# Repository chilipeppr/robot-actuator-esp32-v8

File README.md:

# robot-actuator-esp32-v8
This is the repo for the robot actuator v8 based on an ESP32 as the brains of each robot arm actuator.

This repository contains the latest design for the small actuator including:
- PCB schematic and board file (Eagle)
- Bill of Materials
- Fusion 360 files
- STL files for 3D printing
- NodeMCU ESP32 for Lua firmware with touch module, pulse counter module, RMT TX module, and gpiomatrix module.
- Lua code for actuator
- Link to ChiliPeppr http://chilipeppr.com/arm workspace to control the actuator and to ChiliPeppr ESP32 for Lua workspace for uploading code to the ESP32 device http://chilipeppr.com/esp32
- Heat management test results
- Youtube videos

This actuator is based on the amazing design of Jeff Kerr's (LoboCNC on Thingiverse) 3D printed robot arm WE-R2.4 six axis robot arm. https://www.thingiverse.com/thing:3327968

# Eagle Files

The main PCB board in Eagle.

Top

Bottom

The touch PCB board in Eagle.

# Ordering PCBs

When ordering PCBs, keep in mind the thickness of the main PCB is 1.0 mm while the touch PCB is 1.2 mm. A white soldermask is recommended, but not important.

Main PCB is 1.0 mm thickness

Touch PCB is 1.2 mm thickness

# Fusion 360

The CAD files in Fusion360.

# ChiliPeppr

ChiliPeppr Robot Arm Workspace (Work in progress)
http://chilipeppr.com/arm

ChiliPeppr ESP32 for Lua Workspace for editing/uploading code
http://chilipeppr.com/esp32

# Heat Test

# Youtube Videos

Part 1
https://www.youtube.com/watch?v=tEbJV32GyYU

Part 2
https://www.youtube.com/watch?v=RdmdFIhCo4M

Part 3
https://youtu.be/4o3d7_WZ_DQ

<!-- # Pins Used on ESP32

|GPIO|Used|Input|Output|Notes|
|----|-----|------|-----|
|0|Yes|Yes|Yes|motor.pinDir|
|1|TX pin|OK|debug output at boot|
|2|OK|OK|connected to on-board LED|
|3|OK|RX pin|HIGH at boot|
|4|OK|OK|
|5|OK|OK|outputs PWM signal at boot|
|6|x|x|connected to the integrated SPI flash|
|7|x|x|connected to the integrated SPI flash|
|8|x|x|connected to the integrated SPI flash|
|9|x|x|connected to the integrated SPI flash|
|10|x|x|connected to the integrated SPI flash|
|11|x|x|connected to the integrated SPI flash|
|12|OK|OK|boot fail if pulled high|
|13|OK|OK|
|14|OK|OK|outputs PWM signal at boot|
|15|OK|OK|outputs PWM signal at boot|
|16|OK|OK|
|17|OK|OK|
|18|OK|OK|
|19|OK|OK|
|21|OK|OK|
|22|OK|OK|
|23|OK|OK|
|25|OK|OK|
|26|OK|OK|
|27|OK|OK|
|32|OK|OK|
|33|OK|OK|
|34|OK|input only|
|35|OK|input only|
|36|OK|input only|
|39|OK|input only| -->

# Bill of Materials

| Ref    | Part                                                   |  Price   |  Quantity  |  Ext Price  | URL                                                                                                                                                 | Notes                                                                                                                                                                                                                                                                                                                                                  |
|--------|--------------------------------------------------------|----------|------------|-------------|-----------------------------------------------------------------------------------------------------------------------------------------------------|--------------------------------------------------------------------------------------------------------------------------------------------------------------------------------------------------------------------------------------------------------------------------------------------------------------------------------------------------------|
|        |                                                        |          |            |             |                                                                                                                                                     |                                                                                                                                                                                                                                                                                                                                                        |
|        | PCB                                                    |          |            |  $-         |                                                                                                                                                     |                                                                                                                                                                                                                                                                                                                                                        |
|        | ESP32 Wemos Mini                                       |  $4.05   |  1         |  $4.05      | https://www.aliexpress.com/item/32839344778.html                                                                                                    |                                                                                                                                                                                                                                                                                                                                                        |
|        | 2x10 Pin Header Female for ESP32                       |  $0.12   |  2         |  $0.24      | https://lcsc.com/product-detail/Pin-Header-Female-Header_Boom-Precision-Elec-2-54mm-2-10-Straight-Female-header_C30867.html                         | Solder to the ESP32 board                                                                                                                                                                                                                                                                                                                              |
| C1     | 2x10 Pin Header Male for ESP32                         |  $0.10   |  1         |  $0.10      | https://lcsc.com/product-detail/Pin-Header-Female-Header_Shenzhen-Cankemeng-Headers-Pins-2-10P-2-54mm-Straight-line_C124359.html                    | Solder to main PCB                                                                                                                                                                                                                                                                                                                                     |
|        | DRV8825                                                |  $0.88   |  1         |  $0.88      | https://www.aliexpress.com/item/33010878323.html                                                                                                    | The most popular stepper driver out there. Simple and easy.                                                                                                                                                                                                                                                                                            |
|        | 100uF 50V Capacitor for DRV8825                        |  $0.13   |  1         |  $0.13      | https://lcsc.com/product-detail/Aluminum-Electrolytic-Capacitors-Leaded_PANASONIC-EEUFM1H101_C128473.html                                           | The big capacitor for stepper motor driver                                                                                                                                                                                                                                                                                                             |
|        | DC to DC 24V to 5V Converter                           |  $0.48   |  1         |  $0.48      | https://www.aliexpress.com/item/32796268715.html                                                                                                    | Little board from Aliexpress to get us to 5V on the cheap                                                                                                                                                                                                                                                                                              |
|        | Fan 25mm 12V                                           |  $1.08   |  1         |  $1.08      | https://www.aliexpress.com/item/33026177502.html                                                                                                    | Silent fan that we overdrive to 20v for brief periods if heat spikes, otherwise we leave it off                                                                                                                                                                                                                                                        |
| R3     | Fan Mosfet FDV301N 25V 220mA SOT-23                    |  $0.04   |  1         |  $0.04      | https://lcsc.com/product-detail/MOSFET_ON-Semicon_FDV301N_ON-Semicon-ON-FDV301N_C15310.html                                                         | Allows PWM speed control of fan. Run around 20Hz.                                                                                                                                                                                                                                                                                                      |
| R4     | Fan Diode Protector 100V 300mA SOD-123                 |  $0.02   |  1         |  $0.02      | https://lcsc.com/product-detail/Switching-Diode_DIODES_1N4148W-7-F_1N4148W-7-F_C83528.html                                                          | When fan switches off from Mosfet, it generates back current, so this diode lets it loop back into the fan to get absorbed                                                                                                                                                                                                                             |
|        | Fan 100Ohm gate resistor 0402                          |  $0.01   |  1         |  $0.01      | https://lcsc.com/product-detail/Chip-Resistor-Surface-Mount_100R-100R-1_C106232.html                                                                | Absorbs feedback attenuation                                                                                                                                                                                                                                                                                                                           |
|        | Fan 1MOhm pull-down resistor 0402                      |  $0.01   |  1         |  $0.01      | https://lcsc.com/product-detail/Chip-Resistor-Surface-Mount_1MR-105-5_C144054.html                                                                  | Pulldown resistor to ground to shut off mosfet                                                                                                                                                                                                                                                                                                         |
|        | JST XH Male Connector for fan                          |  $0.04   |  1         |  $0.04      | https://lcsc.com/product-detail/Wire-To-Board-Wire-To-Wire-Connector_JST-Sales-America_B2B-XH-A-LF-SN_JST-Sales-America-B2B-XH-A-LF-SN_C158012.html |                                                                                                                                                                                                                                                                                                                                                        |
|        | JST XH Crimp Connector for fan wire                    |  $0.01   |  2         |  $0.02      | https://lcsc.com/product-detail/New-Arrivals_JST-Sales-America-SXH-001T-P0-6N_C385122.html                                                          | In case you have to reterminate the fan wire, get these crimp connectors. You need a crimp tool.                                                                                                                                                                                                                                                       |
|        | JST XH Female Connector for fan wire                   |  $0.02   |  1         |  $0.02      | https://lcsc.com/product-detail/Rectangular-Connectors-Housings_JST-Sales-America_XHP-2_JST-Sales-America-XHP-2_C144401.html                        | In case you have to reterminate the fan wire, get this female housing to slide the crimp connectors into                                                                                                                                                                                                                                               |
|        | WS2812B White                                          |  $0.15   |  1         |  $0.15      | https://www.aliexpress.com/item/32960205936.html                                                                                                    | Break off one LED and solder to side of PCB at 90 degree angle. Connect center pin to DIN, not DOUT.                                                                                                                                                                                                                                                   |
|        | Red LED 0805                                           |  $0.02   |  3         |  $0.06      | https://lcsc.com/product-detail/Light-Emitting-Diodes-LED_0805-Red-LED-Iv-61mcd-Typ-atIF-20mA_C72037.html                                           | Indicator LEDs                                                                                                                                                                                                                                                                                                                                         |
| R5, R2 | 1KOhm current limit resistor for LED 0402              |  $0.01   |  2         |  $0.02      | https://lcsc.com/product-detail/Chip-Resistor-Surface-Mount_1KR-1001-1_C106235.html                                                                 | The LEDs on the 3.3v bus for step and fan indicator use 1K to give LED about 1ma of current so it lights up very dim, but enough to indicate status.                                                                                                                                                                                                   |
| R6     | 2KOhm current limit resistor for power LED 0402        |  $0.01   |  1         |  $0.01      | https://lcsc.com/product-detail/Chip-Resistor-Surface-Mount_Uniroyal-Elec-0402WGF2001TCE_C4109.html                                                 | The power LED is on a 5v bus. 2K gives it about 1.5ma of current for a dim indicator.                                                                                                                                                                                                                                                                  |
|        | 8 Pin Female Header 2.54mm                             |  $0.14   |  2         |  $0.28      | https://lcsc.com/product-detail/Pin-Header-Female-Header_Changjiang-Connectors-A2541HWV-8P_C225505.html                                             | 2 needed for DRV8825 connection to main PCB.                                                                                                                                                                                                                                                                                                           |
|        | 4 Pin Female Header 2.54mm                             |  $0.07   |  3         |  $0.22      | https://lcsc.com/product-detail/Pin-Header-Female-Header_Shenzhen-Cankemeng-Female-header-1-4P-2-54mm-Straight-line_C124413.html                    | 1 for DC to DC, 2 for touch sensor PCB connection                                                                                                                                                                                                                                                                                                      |
|        | 3 Pin Female Header 2.54mm                             |  $0.06   |  2         |  $0.11      | https://lcsc.com/product-detail/Pin-Header-Female-Header_Shenzhen-Cankemeng-22025403P00CKMT_C146690.html                                            | One for Hall sensor, one for TMP36.                                                                                                                                                                                                                                                                                                                    |
|        | 2 Pin Female Header 2.54mm                             |  $0.03   |  4         |  $0.10      | https://lcsc.com/product-detail/Pin-Header-Female-Header_Boom-Precision-Elec-2-54-1-2PFemale_C49661.html                                            | 2 for incoming 20v from slip ring. 2 for outgoing 20v to slip ring.                                                                                                                                                                                                                                                                                    |
|        | JST PH B4B-K-S Male Header for Stepper                 |  $0.17   |  1         |  $0.17      | https://lcsc.com/product-detail/Wire-To-Board-Wire-To-Wire-Connector_JST-Sales-America_B4B-PH-K-LF-SN_JST-Sales-America-B4B-PH-K-LF-SN_C265289.html | Socket soldered to PCB                                                                                                                                                                                                                                                                                                                                 |
|        | JST PHR-4 Female Header for Stepper Cable              |  $0.02   |  1         |  $0.02      | https://lcsc.com/product-detail/Connectors_JST_PHR-4_PHR-4-4P-pitch2-0mm-Plastic-shell_C111514.html                                                 | End of wire crimped connector                                                                                                                                                                                                                                                                                                                          |
| C2     | JST SPH Crimp Connector                                |  $0.01   |  4         |  $0.03      | https://lcsc.com/product-detail/Rectangular-Connectors-Contacts_JST_SPH-002T-P0-5S_SPH-002T-P0-5S-PH-T-PH-2-0_C111515.html                          | Individual crimp connectors. You'll need a crimping tool.                                                                                                                                                                                                                                                                                              |
|        | Toggle Switch                                          |  $0.12   |  1         |  $0.12      | https://lcsc.com/product-detail/Toggle-Switches_Korean-Hroparts-Elec-K3-1260D-L1_C92657.html                                                        | Toggle on/off the 20v to all components                                                                                                                                                                                                                                                                                                                |
|        | Pin Male Header Right Angle 2.54mm (40 pins breakaway) |  $0.44   |  2         |  $0.88      | https://www.digikey.com/product-detail/en/0022286043/WM22771-ND/3158673                                                                             | Right angle needed for touch sensor connection. Actually, I had to create my own right angle ones from straight ones to be long enough. They need to be about 10mm long from the touch PCB down to the pin headers, so buy the longest straight ones you can and bend them, then cut to size after you try to fit. Or, you can buy them from digikey.  |
|        | Pin Male Header Straight 2.54mm (40 pins breakaway)    |  $0.14   |  1         |  $0.14      | https://lcsc.com/product-detail/Pin-Header-Female-Header_Nextronics-Engineering-Z-211-4011-0021-001_C113597.html                                    | Break off all headers for the numerous areas that need a male header pin.                                                                                                                                                                                                                                                                              |
|        | 0.1uF Capacitor smoothing for TMP36                    |  $0.01   |  1         |  $0.01      | https://lcsc.com/product-detail/Others_Vishay-Intertech_VJ0402G104KXQCW1BC_Vishay-Intertech-VJ0402G104KXQCW1BC_C169292.html                         | TMP36 can give somewhat noisy temperature measurements. This cap on the input 3.3v on sensor can smooth out the output readings. You can operate without this cap since the software does multiple readings to average it.                                                                                                                             |
|        |                                                        |          |            |             |                                                                                                                                                     |                                                                                                                                                                                                                                                                                                                                                        |
|        | Actuator                                               |          |            |  $-         |                                                                                                                                                     |                                                                                                                                                                                                                                                                                                                                                        |
|        | Stepper Motor 35mm                                     |  $2.90   |  1         |  $2.90      | https://www.aliexpress.com/item/2054451318.html                                                                                                     | Cut off the PCB and resolder the 4 Pin silicone wire to the leads on the stepper. Make wire long enough you can connect to PCB while it's outside the actuator, around 4 to 6 inches.                                                                                                                                                                  |
|        | Neodymium Disc Mini Magnet 3x1.5mm                     |  $0.05   |  1         |  $0.05      | https://www.aliexpress.com/item/32949884024.html                                                                                                    | Magnet needed to trigger hall effect sensor                                                                                                                                                                                                                                                                                                            |
|        | Hall Effect Sensor SIP-3                               |  $0.14   |  1         |  $0.14      | https://lcsc.com/product-detail/Sensors_SK1816G-G03-K_C73293.html                                                                                   | Place into slot on bottom of 3D printed actuator, then place compression 3D printed backing to keep in place as close to magnet as you can.                                                                                                                                                                                                            |
|        | Heatsink 540/550 Motor                                 |  $1.00   |  1         |  $1.00      | https://www.aliexpress.com/item/33004830927.html                                                                                                    | Cut heatsink in half to service 2 actuators                                                                                                                                                                                                                                                                                                            |
|        | 4 Pin 30AWG Silicone Wire Ultra Flexible               |  $0.24   |  1         |  $0.24      | https://www.aliexpress.com/item/32870367030.html                                                                                                    | Use this wire to connect hall effect and TMP36 sensors to main PCB. Solder 3 wires to each sensor and then to 2.54mm standard 3 pin female headers.                                                                                                                                                                                                    |
|        | TMP36 Temperature Sensor TO-92                         |  $1.08   |  1         |  $1.08      | https://lcsc.com/product-detail/Temperature-Sensors_ADI_TMP36GT9Z_TMP36GT9Z_C53490.html                                                             | Temperature sensor is pushed against stepper motor to watch motor temp as it can get hot and melt the 3D printed parts, ruining the actuator.                                                                                                                                                                                                          |
|        |                                                        |          |            |  $-         |                                                                                                                                                     |                                                                                                                                                                                                                                                                                                                                                        |
|        |                                                        |  $13.78  |            |  $14.84     |                                                                                                                                                     |                                                                                                                                                                                                                                                                                                                                                        |
|        |                                                        |          |            |             |                                                                                                                                                     |                                                                                                                                                                                                                                                                                                                                                        |
|        |                                                        |          |            |             |                                                                                                                                                     |                                                                                                                                                                                                                                                                                                                                                        |
|        | Other Stepper Motors                                   |          |            |             |                                                                                                                                                     |                                                                                                                                                                                                                                                                                                                                                        |
|        | Higher end 35mm stepper Moon's                         |  $25.00  |  1         |  $25.00     | https://www.moonsindustries.com/p/35mm-permanent-magnet-stepper-motors/35pm048s8-08001-000004611120001819                                           | Not sure it's worth the money, but this motor is nice. I'm finding the cheaper motors are just about as good, but perhaps not as quiet or tight feeling as the Moon's.                                                                                                                                                                                 |
|        | Another cheap 35mm that's really nice                  |  $3.00   |  1         |  $3.00      | https://www.aliexpress.com/item/32975464158.html                                                                                                    | This is a very nice motor and cheap, but you have to grind off the gear on the 3mm shaft, which is painful.                                                                                                                                                                                                                                            |

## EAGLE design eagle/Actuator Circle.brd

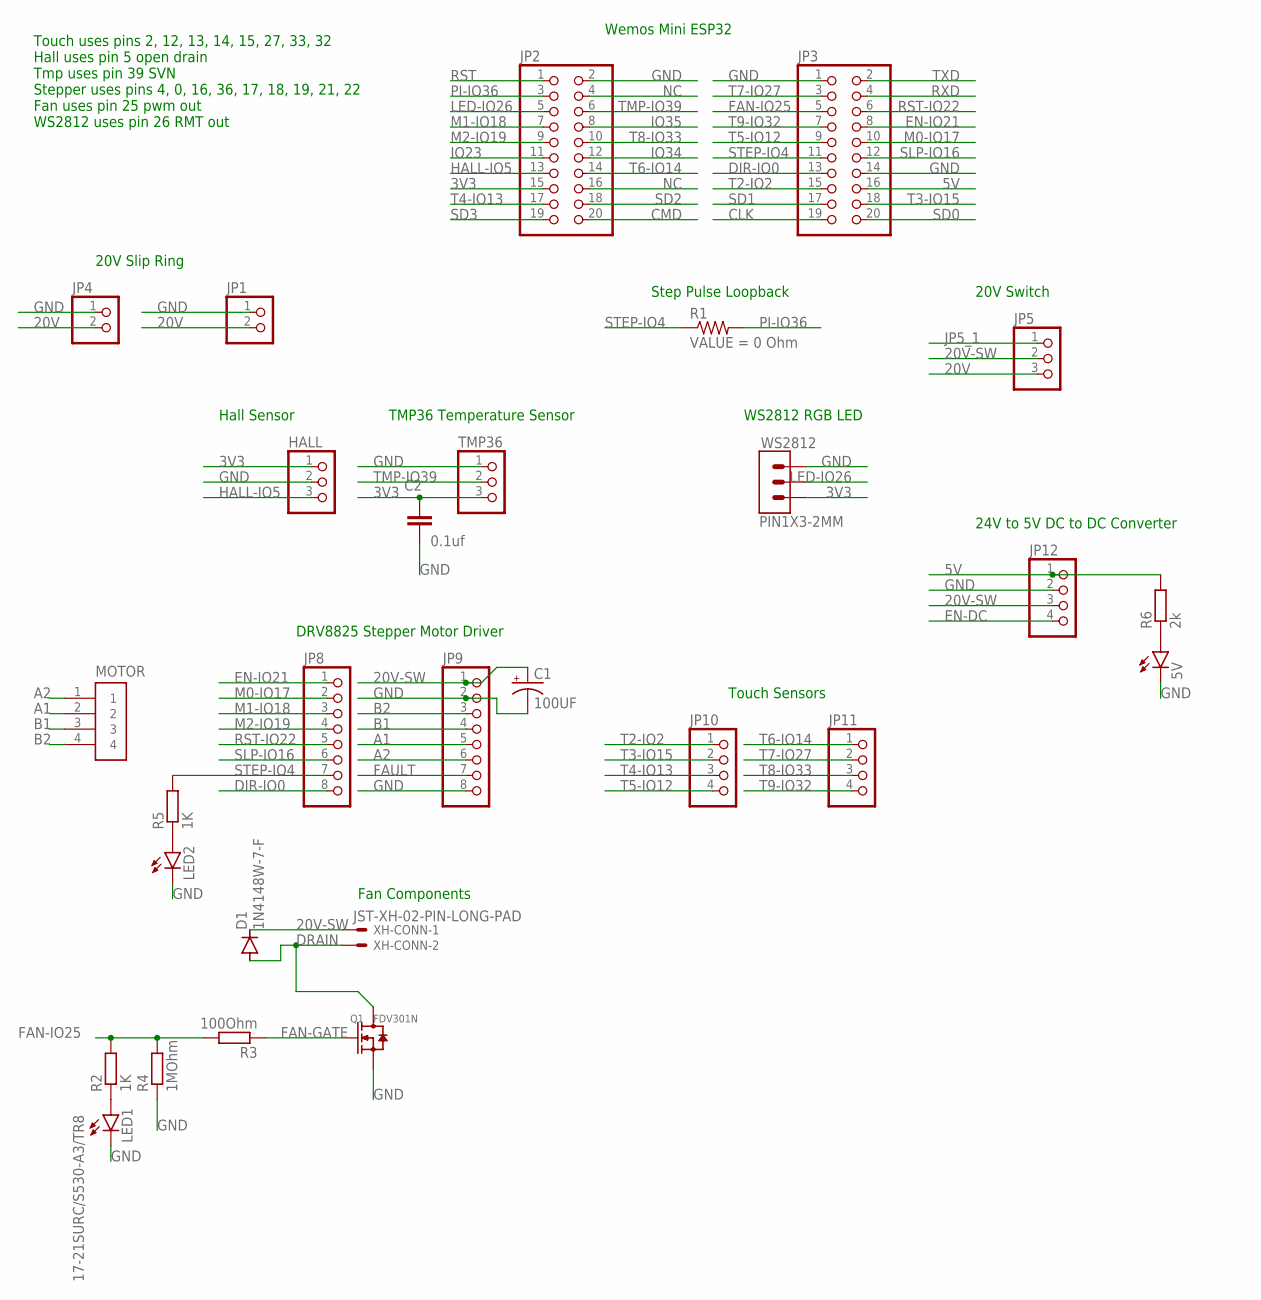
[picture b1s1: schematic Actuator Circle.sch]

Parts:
5V: 17-21SURC/S530-A3/TR8; CHIPLED_0805
C1: 100UF; E2,5-6
C2: 0.1uf; CAP_0603
D1: 1N4148W-7-F; SOD123
HALL: PINHD-1X3; 1X03
JP1, JP4: PINHD-1X2; 1X02
JP2, JP3: PINHD-2X10; 2X10
JP5: PINHD-1X3/90; 1X03/90
JP8, JP9: PINHD-1X8; 1X08
JP10, JP11, JP12: PINHD-1X4; 1X04
LED1, LED2: 17-21SURC/S530-A3/TR8; CHIPLED_0805
MOTOR: B4B-PH-K-S(LF)(SN); JST_B4B-PH-K-S(LF)(SN)
Q1: FDV301N; SOT23
R1: 0 Ohm; RES_0402
R2, R5: 1K; R0603
R3: 100Ohm; R0603
R4: 1MOhm; R0603
R6: 2k; R0603
TMP36: PINHD-1X3; 1X03
WS2812: PIN1X3-2MM
XH-CONN: JST-XH-02-PIN-LONG-PAD; JST-XH-02-PACKAGE-LONG-PAD

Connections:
3V3: C2.1, HALL.1, JP2.15, TMP36.3, WS2812.3
5V: JP3.16, JP12.1, R6.2
20V: JP1.2, JP4.2, JP5.3
20V-SW: C1.+, D1.1 (C), JP5.2, JP9.1, JP12.3, XH-CONN.1
A1: JP9.5, MOTOR.2
A2: JP9.6, MOTOR.1
B1: JP9.4, MOTOR.3
B2: JP9.3, MOTOR.4
CLK: JP3.19
CMD: JP2.20
DIR-IO0: JP3.13, JP8.8
DRAIN: D1.2 (A), Q1.3 (D), XH-CONN.2
EN-DC: JP12.4
EN-IO21: JP3.8, JP8.1
FAN-GATE: Q1.1 (G), R3.1
FAN-IO25: JP3.5, R2.2, R3.2, R4.2
FAULT: JP9.7
GND: 5V.C, C1.-, C2.2, HALL.2, JP1.1, JP2.2, JP3.1, JP3.14, JP4.1, JP9.2, JP9.8, JP12.2, LED1.C, LED2.C, Q1.2 (S), R4.1, TMP36.1, WS2812.1
HALL-IO5: HALL.3, JP2.13
IO23: JP2.11
IO34: JP2.12
IO35: JP2.8
JP5_1: JP5.1
LED-IO26: JP2.5, WS2812.2
M0-IO17: JP3.10, JP8.2
M1-IO18: JP2.7, JP8.3
M2-IO19: JP2.9, JP8.4
unnamed: LED1.A, R2.1
unnamed: LED2.A, R5.1
unnamed: 5V.A, R6.1
NC: JP2.4, JP2.16
PI-IO36: JP2.3, R1.2
RST: JP2.1
RST-IO22: JP3.6, JP8.5
RXD: JP3.4
SD0: JP3.20
SD1: JP3.17
SD2: JP2.18
SD3: JP2.19
SLP-IO16: JP3.12, JP8.6
STEP-IO4: JP3.11, JP8.7, R1.1, R5.2
T2-IO2: JP3.15, JP10.1
T3-IO15: JP3.18, JP10.2
T4-IO13: JP2.17, JP10.3
T5-IO12: JP3.9, JP10.4
T6-IO14: JP2.14, JP11.1
T7-IO27: JP3.3, JP11.2
T8-IO33: JP2.10, JP11.3
T9-IO32: JP3.7, JP11.4
TMP-IO39: JP2.6, TMP36.2
TXD: JP3.2

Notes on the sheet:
Touch Sensors
DRV8825 Stepper Motor Driver
Wemos Mini ESP32
Fan Components
24V to 5V DC to DC Converter
20V Slip Ring
Hall Sensor
TMP36 Temperature Sensor
WS2812 RGB LED
Touch uses pins 2, 12, 13, 14, 15, 27, 33, 32 Hall uses pin 5 open drain Tmp uses pin 39 SVN Stepper uses pins 4, 0, 16, 36, 17, 18, 19, 21, 22 Fan uses pin 25 pwm out WS2812 uses pin 26 RMT out
Step Pulse Loopback
20V Switch

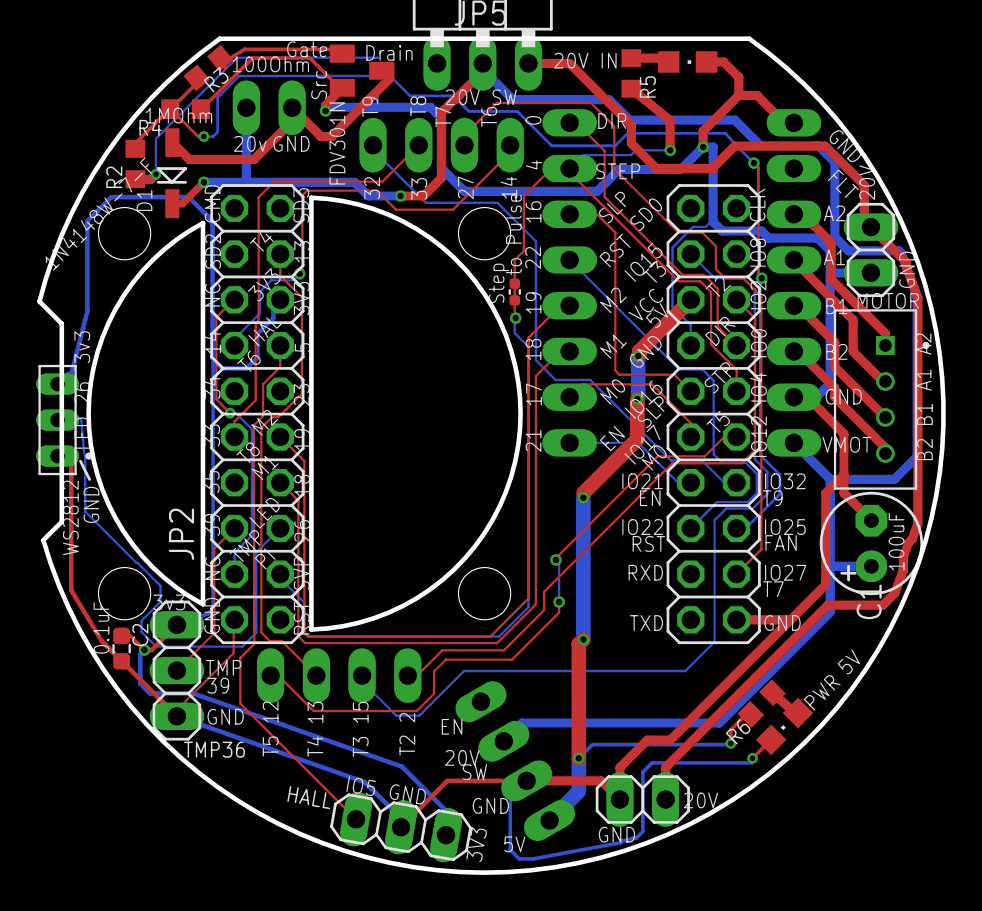
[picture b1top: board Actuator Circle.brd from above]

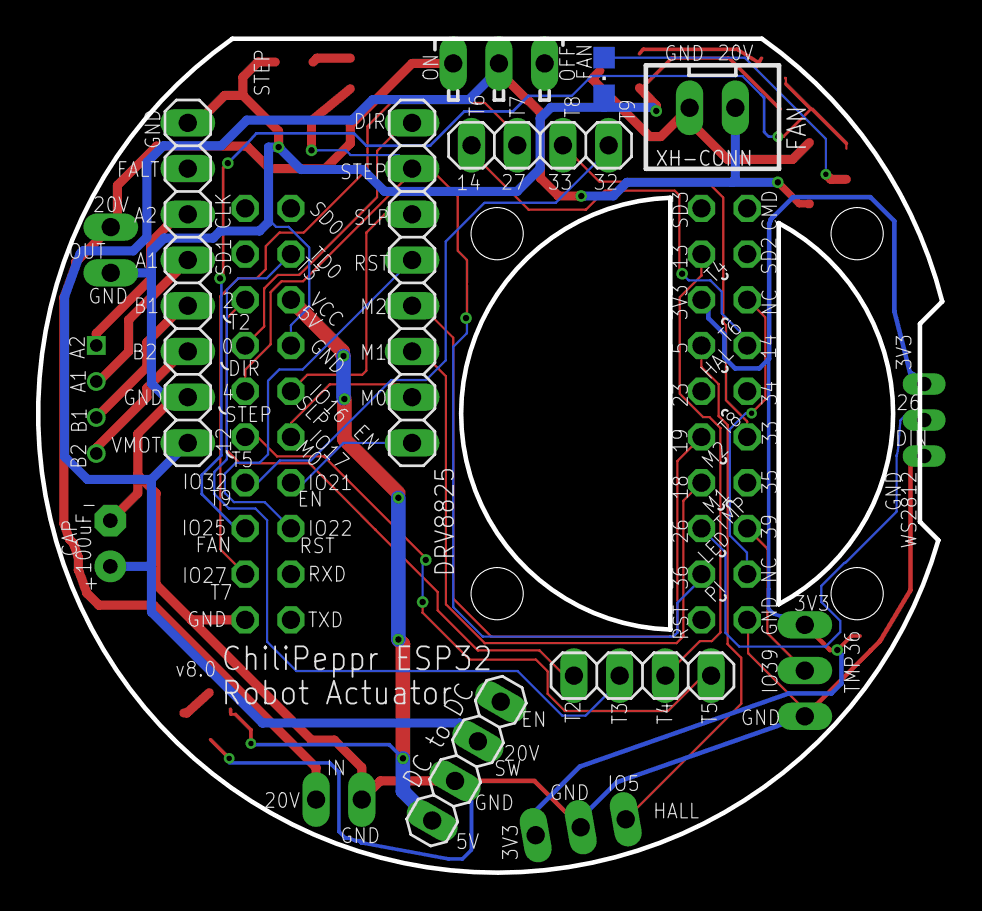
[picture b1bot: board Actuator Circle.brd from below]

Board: 2 copper layers, 50.2 x 46.3 mm, 28 parts (7 on the bottom side), 36 nets.

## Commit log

2019-09-30 first check in
2019-09-30 more images
2019-10-06 More readme content
2019-10-14 added acrylic balls
2019-10-25 Modified Resistors to 0603, and moved them to the same side
    Modified Resistors to 0603, and moved them to the same side, so as to make assembly slightly easier.
2019-10-29 BOM and Pick Place for SMT Assembly
2019-11-27 Latest version
2019-11-27 Latest 2
2019-11-27 oct 4th firmware build
2019-11-27 Update Actuator Circle.brd
    Moved the vias further away from the top side resistors. Also covered vias with solder mask to minimise risk of shorts whilst soldering
